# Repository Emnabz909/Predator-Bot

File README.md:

# Heat-Seeking Predator Bot

This project involved designing and building an autonomous robot capable of tracking and following a person based on their heat signature. The bot integrates various sensors, actuators, and a custom PCB for hardware interfacing, exemplifying a multidisciplinary approach to mechatronics.

## Table of Contents
1. [Introduction](#introduction)
2. [Specifications](#specifications)
3. [Design Development](#design-development)
   - [Hardware Design](#hardware-design)
   - [Software Design](#software-design)
4. [Results](#results)
5. [Lessons Learned](#lessons-learned)
6. [References](#references)

---

## Introduction
The Heat-Seeking Predator Bot was designed to:
- Detect and follow a person using a thermal camera and IR distance sensor.
- Maintain a proximity range using motor control.
- Demonstrate multitasking capabilities for real-time operation.

The bot was built using an ESP32 FireBeetle microcontroller, with custom PCB and housing, leveraging various sensors and actuators to create a functional prototype.

## Specifications
The bot's key specifications are:
- **Thermal Camera**: Adafruit MLX90640 (20–40°C, ±5°C accuracy).
- **IR Distance Sensor**: Sharp GP2Y0A21YK0F (2–36 inches, ±0.5-inch accuracy).
- **Inertial Measurement Unit (IMU)**: Adafruit BNO055 for motion control.
- **Motors**: N20 DC motors with magnetic encoders and DRV8871 motor drivers.

### Pass/Fail Criteria
- Tracks heat signatures.
- Maintains a 2–36-inch range from objects.
- Streams thermal heatmaps to a web interface.

---

## Design Development

### Hardware Design
The custom PCB was created using KiCAD and included:
- Screw terminals for component connectivity.
- Proper trace sizing for power and heat dissipation.
- Compact layout to minimize weight and improve balance.

The bot’s housing was designed to securely hold all components while minimizing weight-induced friction.

### Software Design
The software was modular, focusing on individual sensor functionality before integration:
- **Thermal Camera**: Detected heat signatures and converted data to ASCII for debugging.
- **IR Distance Sensor**: Measured distance using voltage-to-distance calibration.
- **IMU**: Provided acceleration data to refine motor control.
- **Motor Control**: Implemented PID for speed adjustments.

Due to time constraints, full system integration was not achieved.

---

## Results
While the bot's PCB design required significant revisions, the sensors functioned as expected when tested individually. Challenges included:
- Inadequate motor speed and torque.
- Integration of components due to missing PCB features.

Despite these setbacks, the project provided valuable hands-on experience.

---

## Lessons Learned
Key takeaways include:
1. **Early Planning**: A thorough design phase and literature review are essential.
2. **PCB Design**: Focus on component connectivity, power handling, and adequate debugging options.
3. **Prototyping**: Iterative testing is vital for identifying and resolving design flaws.

---

## References
- [Adafruit MLX90640 GitHub Repository](https://github.com/adafruit/Adafruit_MLX90640)
- [Adafruit BNO055 GitHub Repository](https://github.com/adafruit/Adafruit_BNO055)
- [Predator Bot Repository](https://github.com/Emnabz909/Predator-Bot)

---

## Acknowledgments
This project was completed as part of ME 507 at Cal Poly San Luis Obispo. Special thanks to the Mechatronics Department for providing resources and support.

---

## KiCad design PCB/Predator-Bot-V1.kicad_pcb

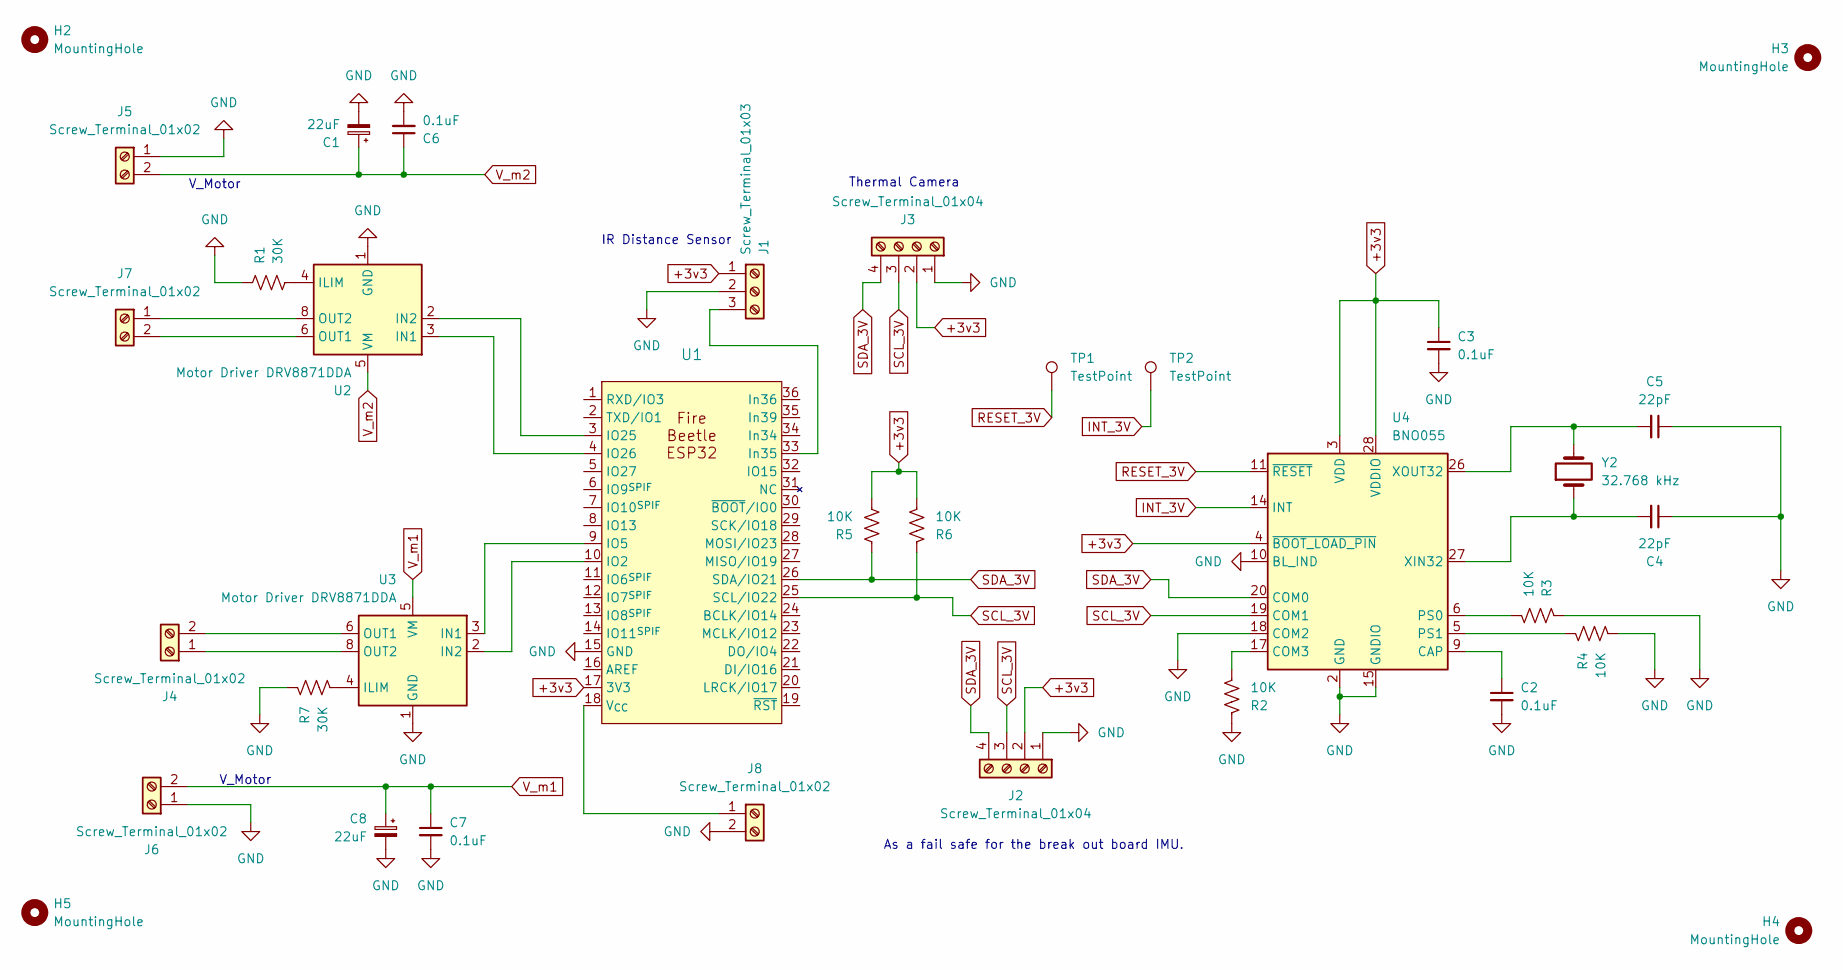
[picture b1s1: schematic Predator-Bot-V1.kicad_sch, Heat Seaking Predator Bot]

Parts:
C1, C8: 22uF; C_0805_2012Metric
C2, C3, C6, C7: 0.1uF; C_0805_2012Metric
C4, C5: 22pF; C_0805_2012Metric
H2, H3, H4, H5: MountingHole; MountingHole_3.5mm
J1: Screw_Terminal_01x03; TerminalBlock_Phoenix_MPT-0,5-3-2.54_1x03_P2.54mm_Horizontal
J2, J3: Screw_Terminal_01x04; TerminalBlock_Phoenix_MPT-0,5-4-2.54_1x04_P2.54mm_Horizontal
J4, J5, J6, J7, J8: Screw_Terminal_01x02; TerminalBlock_Phoenix_MPT-0,5-2-2.54_1x02_P2.54mm_Horizontal
R1, R7: 30K; R_0805_2012Metric
R2, R3, R4, R5, R6: 10K; R_0805_2012Metric
TP1, TP2: TestPoint; TestPoint_Plated_Hole_D2.0mm
U1: FireBeetle-ESP32
U2, U3: Motor Driver DRV8871DDA; Texas_HTSOP-8-1EP_3.9x4.9mm_P1.27mm_EP2.95x4.9mm_Mask2.4x3.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
U4: BNO055; LGA-28_5.2x3.8mm_P0.5mm
Y2: 32.768 kHz; Crystal_C26-LF_D2.1mm_L6.5mm_Horizontal

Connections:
+3v3: C3.1, J1.1, J2.2, J3.2, R5.2, R6.2, U1.17 (3V3), U4.3 (VDD), U4.4 (~BOOT_LOAD_PIN), U4.28 (VDDIO)
GND: C1.2, C2.2, C3.2, C4.1, C5.1, C6.2, C7.2, C8.2, J1.2, J2.1, J3.1, J5.1, J6.1, J8.2, R1.1, R2.1, R3.1, R4.2, R7.1, U1.15 (GND), U2.1 (GND), U2.7 (GND), U2.9 (GND), U3.1 (GND), U3.7 (GND), U3.9 (GND), U4.2 (GND), U4.10 (BL_IND), U4.15 (GNDIO), U4.16 (GNDIO), U4.18 (COM2), U4.25 (GNDIO)
INT_3V: TP2.1, U4.14 (INT)
unnamed: J1.3, U1.33 (In35)
unnamed: J4.1, U3.8 (OUT2)
unnamed: J4.2, U3.6 (OUT1)
unnamed: J7.1, U2.8 (OUT2)
unnamed: J7.2, U2.6 (OUT1)
unnamed: J8.1, U1.18 (V_{CC})
unnamed: U1.10 (IO2), U3.2 (IN2)
unnamed: U1.9 (IO5), U3.3 (IN1)
unnamed: U1.3 (IO25), U2.2 (IN2)
unnamed: U1.4 (IO26), U2.3 (IN1)
unnamed: R1.2, U2.4 (ILIM)
unnamed: R7.2, U3.4 (ILIM)
unnamed: C2.1, U4.9 (CAP)
unnamed: R2.2, U4.17 (COM3)
unnamed: R3.2, U4.6 (PS0)
unnamed: R4.1, U4.5 (PS1)
unnamed: C4.2, U4.27 (XIN32), Y2.1
unnamed: C5.2, U4.26 (XOUT32), Y2.2
RESET_3V: TP1.1, U4.11 (~RESET)
SCL_3V: J2.3, J3.3, R6.1, U1.25 (SCL/IO22), U4.19 (COM1)
SDA_3V: J2.4, J3.4, R5.1, U1.26 (SDA/IO21), U4.20 (COM0)
V_m1: C7.1, C8.1, J6.2, U3.5 (VM)
V_m2: C1.1, C6.1, J5.2, U2.5 (VM)

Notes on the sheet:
IR Distance Sensor
As a fail safe for the break out board IMU.
V_Motor
Thermal Camera

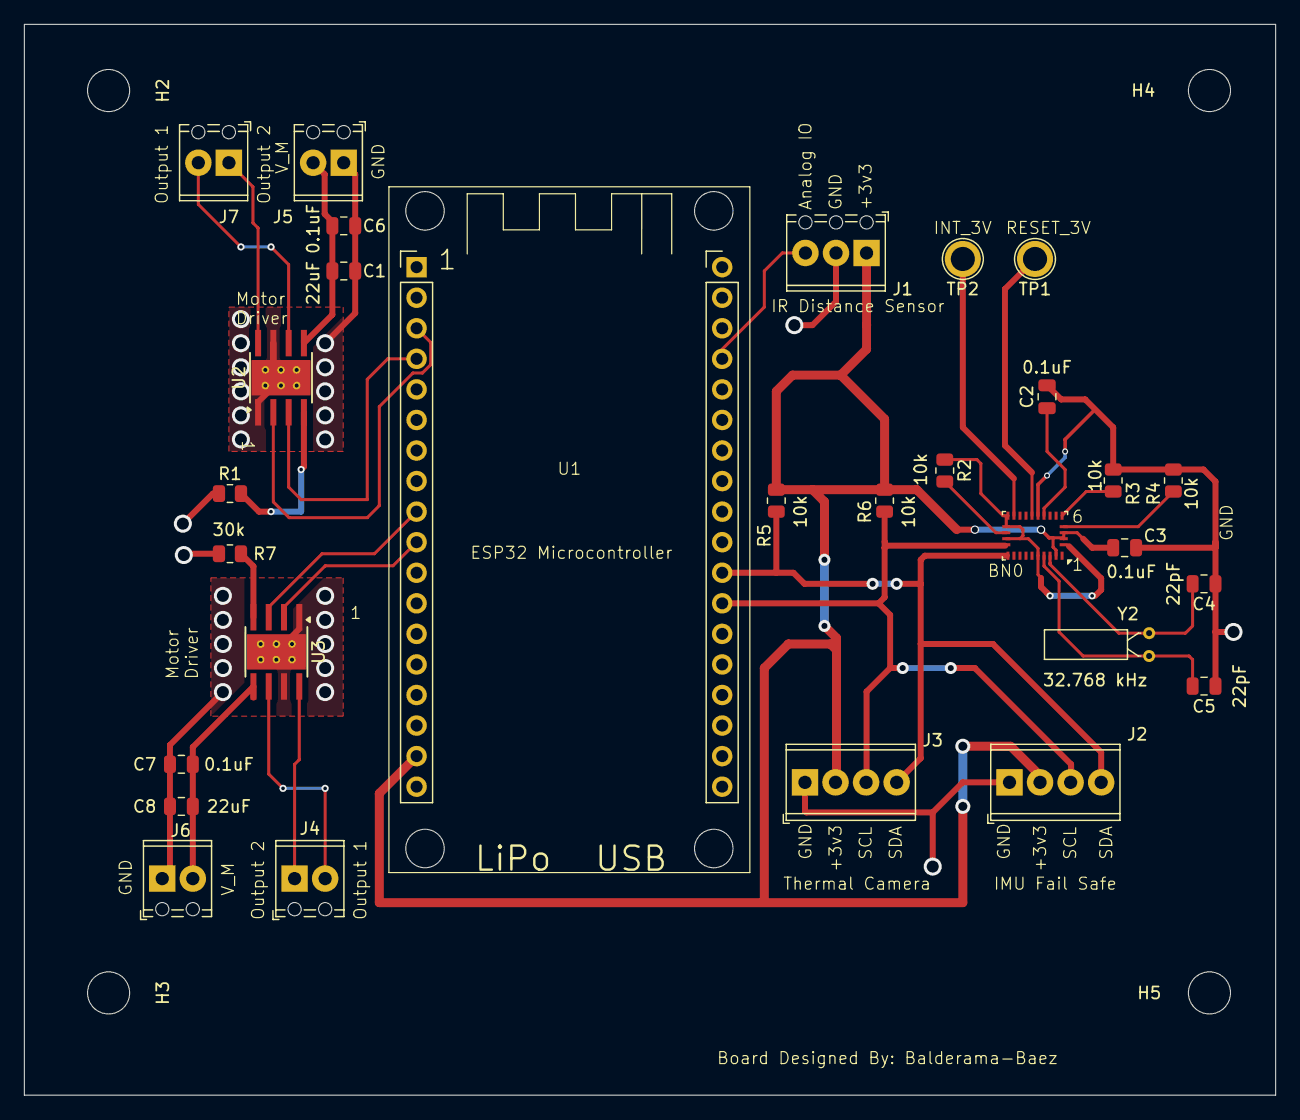
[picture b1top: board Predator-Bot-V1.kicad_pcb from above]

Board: 2 copper layers, 104.0 x 89.0 mm, 33 parts (0 on the bottom side), 25 nets.
